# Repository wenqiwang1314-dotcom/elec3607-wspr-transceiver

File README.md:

# ELEC3607 Assignment 1: WSPR Transceiver 任务设计

版本依据：Assignment 1 - WSPR Transceiver Version 0.4, 15 Apr 2026  
工程目录：`pcb_2026`  
原始 KiCad 工程：`bbb.kicad_pro`, `bbb.kicad_sch`, `bbb.kicad_pcb`  
最终提交：单个 `.zip`，包含 KiCad schematic、PCB design files、IEEE conference format 报告。

## 1. 项目目标

本项目在实验课 WSPR-SDR 接收机基础上完成两个修改：

1. Part A：用 Si5351 剩余的 `CLK2` 输出实现 WSPR 发射软件，并通过硬连线 RF loopback 让已有接收机或教师 decoder board 解码。
2. Part B：从现有 PCB 出发，重新设计成收发一体 transceiver PCB。发射机输出需达到 `0.1 W into 50 ohms`，收发共用接收机 bandpass filter，收发切换由 GPIO 控制，新增器件来自 Element14 Australia。

评分重点不是解释旧 WSPR-SDR，而是清楚说明新增发射功能、RF loopback、功率放大、收发切换和 PCB 修改如何工作。

## 2. 本地 Resources 使用清单

| 资料 | 用途 |
|---|---|
| `Resources/wspr_coding_process.pdf` | Part A WSPR message 编码、symbol 生成、tone mapping 的主要依据。 |
| `Resources/Si5351-B.pdf` | Si5351 `CLK2` 输出频率、驱动强度、寄存器/I2C 控制和硬件限制。 |
| `Resources/QS11-2010-Taylor.pdf` | WSPR 协议背景、4-FSK、tone spacing、解码约束和报告引用。 |
| `Resources/Tayloe_mixer_x3a.pdf` | 原接收机 quadrature sampling/Tayloe mixer 信号路径说明。 |
| `Resources/A Comparison of Affordable, Self-Assembled Software-Defined Radio Receivers Using Quadrature Sampling Down-Conversion.pdf` | 报告风格和 SDR 接收架构描述参考。 |
| `Resources/ABCs of Probes 60W-6053-15.pdf` | 示波器探头、RF/低电平测量误差说明。 |
| `Resources/emc_and_signal_integrity_ce_magazine_march-april_1999.pdf` | PCB layout、RF grounding、return path 和串扰风险说明。 |
| `Resources/website.txt` | WSPR/SDR 相关网页入口。 |

## 3. 团队分工建议

| 角色 | 主要负责 | 输出物 |
|---|---|---|
| Software lead | `wspr_transmit` C 程序、WSPR 编码、Si5351 `CLK2` 控制、CLI 参数验证 | C 源码、运行说明、软件测试记录 |
| Hardware modification lead | Part A 现有 PCB 飞线/RF loopback/衰减网络/照片/测量 | 修改原理图、PCB 照片、测试数据 |
| RF/PCB lead | Part B PA、T/R switch、共享 BPF、KiCad schematic/PCB layout | 更新后的 `.kicad_sch`, `.kicad_pcb`, BOM |
| Report/integration lead | IEEE 报告、图表、参考文献、提交 zip 检查 | 4 页以内 PDF 报告、最终 zip |

每个人都需要能在 oral discussion 中解释自己部分之外的完整信号路径。

## 4. Part A 任务：WSPR 发射与 RF Loopback

### A1. 明确 WSPR 发射需求

- 输入格式：`./wspr_transmit CALLSIGN LOCATOR POWER`
- 示例：`./wspr_transmit VK2AAX QF56 3`
- CLI 参数检查：
  - callsign：合法 WSPR callsign 格式，报告中说明支持范围。
  - locator：4 字符 Maidenhead grid，例如 `QF56`。
  - power：WSPR dBm power code，示例 `3` 代表作业要求输入格式，实际含义需在报告中解释。
- 输出信号：
  - WSPR uses 4-FSK.
  - 每个 symbol 选择 4 个 tone 之一。
  - tone spacing 约 `1.4648 Hz`。
  - 一帧 WSPR 标准消息共 `162` symbols，持续约 `110.6 s`。
- 软件必须使用 Si5351 `CLK2` 产生 RF tone，不使用空中发射。

完成标准：

- 程序能接受示例命令并生成确定的 WSPR symbol/tone 序列。
- 参数错误时给出 usage。
- 报告中给出 symbol generation 流程图或伪代码。

### A2. 编写 `wspr_transmit` C 程序

建议文件：

- `software/wspr_transmit.c`
- `software/wspr_encode.c`
- `software/wspr_encode.h`
- `software/si5351_control.c`
- `software/si5351_control.h`
- `software/Makefile`

软件模块任务：

1. `main()` 解析 `CALLSIGN LOCATOR POWER`。
2. WSPR message packing：将 callsign、locator、power 打包成 WSPR message bits。
3. FEC/interleaving/sync：按 `Resources/wspr_coding_process.pdf` 生成 162 个 symbols。
4. Tone scheduler：将 symbol 映射到 `f0 + symbol * 1.4648 Hz`。
5. Si5351 driver：通过 I2C 更新 `CLK2` 输出频率。
6. Timing：每个 symbol 周期约 `110.592 / 162 = 0.6827 s`，尽量减少切换抖动。
7. Logging：启动时打印 callsign、locator、power、base frequency、frame start time。

建议测试：

- Unit test：固定输入 `VK2AAX QF56 3` 时 symbol 序列可重复。
- Dry run：不控制 Si5351，只打印 tone frequency 和 symbol index。
- Hardware run：连接示波器/频率计确认 `CLK2` 有 4 个细小频偏。

完成标准：

- `make` 后生成 `wspr_transmit`。
- `./wspr_transmit VK2AAX QF56 3` 能运行完整帧。
- 报告附核心 C 代码片段，不必粘贴全部文件。

### A3. 音频 loopback 小步验证

用途：在 RF loopback 之前先验证编码和解码链路。

任务：

- 生成等效 audio baseband 4-FSK tone 序列。
- 将 audio 输出接入现有接收/解码链路。
- 用实验室 receiver/decoder 确认 callsign、locator、power 可解出。

完成标准：

- 记录一次成功 decode 的截图或串口/终端输出。
- 在报告中说明 audio loopback 只是中间验证，不是最终 RF 方案。

### A4. RF loopback 硬件修改

目标：将 Si5351 `CLK2` RF 输出硬连线接回 receiver RF input，不经过天线空中传播。

建议电路：

```text
Si5351 CLK2
    |
    |-- DC blocking capacitor
    |
  resistive attenuator / level-setting network
    |
    |-- optional test point
    |
receiver RF input before existing bandpass/mixer chain
```

关键设计点：

- 不应直接把过大的 `CLK2` 方波灌入 receiver input。
- 通过电容隔直和电阻衰减控制接收机输入电平。
- 尽量保持短接线、公共地可靠、避免 RF pickup。
- 报告需要包含：
  - 修改电路图。
  - 修改后 PCB 照片。
  - 衰减网络计算。
  - 实测 `CLK2` 输出幅度、receiver input 幅度、decode 结果。

完成标准：

- 教师 decoder board 或本组 WSPR receiver 能从 RF loopback 解码。
- 测量记录包含仪器型号/探头设置/测量点。

### A5. Part A 测量清单

| 测量项 | 测量点 | 期望记录 |
|---|---|---|
| `CLK2` RF 输出 | Si5351 `CLK2` 或飞线起点 | 频率、幅度、波形 |
| 衰减后 RF | receiver input | 幅度，确认不会过载 |
| Tone spacing | `CLK2` 或 receiver output | 约 `1.4648 Hz` 间隔，或解释仪器分辨率限制 |
| Decode 结果 | WSPR receiver/decoder | callsign、locator、power、SNR/time offset/frequency offset |
| 电源电流 | 板级输入 | RX/TX 状态对比 |

## 5. Part B 任务：Transceiver PCB 设计

### B1. 建立 KiCad 修改分支

任务：

- 复制原始工程，避免破坏 baseline。
- 建议新文件命名：
  - `wspr_transceiver.kicad_pro`
  - `wspr_transceiver.kicad_sch`
  - `wspr_transceiver.kicad_pcb`
- 保持 PCB 外形尺寸与原始 `bbb.kicad_pcb` 一致。
- 保留原接收机必要链路，只修改收发相关电路。

完成标准：

- KiCad ERC/DRC 主要错误已处理或在报告中解释。
- 原始板框尺寸未改变。

### B2. Part B RF 信号路径定义

建议完整信号路径：

```text
TX mode:
Si5351 CLK2
 -> output shaping / attenuator
 -> driver / PA
 -> low-pass or harmonic filtering if required
 -> GPIO-controlled T/R switch
 -> shared bandpass filter
 -> 50 ohm RF output / loopback/test connector

RX mode:
50 ohm RF input
 -> GPIO-controlled T/R switch
 -> shared bandpass filter
 -> existing receiver mixer / audio chain
```

报告必须说明：

- GPIO 为 RX 时，PA 输出不能反灌 receiver。
- GPIO 为 TX 时，receiver input 被隔离或保护。
- Bandpass filter 被 TX 和 RX 共用，符合题目要求。
- 50 ohm 系统如何匹配。

### B3. 0.1 W into 50 ohms 设计计算

设计目标：

- 输出功率：`Pout = 0.1 W = 20 dBm`
- 负载：`R = 50 ohms`
- 正弦波等效：
  - `Vrms = sqrt(P * R) = sqrt(0.1 * 50) = 2.236 V`
  - `Vpk = 3.162 V`
  - `Vpp = 6.324 V`
  - `Irms = Vrms / R = 44.7 mA`

任务：

- 选择 PA 架构：小信号 driver + RF transistor/MOSFET，或可买到的 RF gain block/PA 器件。
- 计算所需 gain：由 Si5351 `CLK2` 可用输出电平推算到 `20 dBm`。
- 设计输出匹配网络和 bias。
- 检查功耗和热耗散。
- 检查 harmonic suppression，必要时加入 LPF 或利用共享 BPF 后的选择性。

完成标准：

- 报告给出 PA 电路图、关键元件值、偏置点、预期 gain、预期输出功率。
- BOM 中新增器件来自 Element14 Australia，并记录订购编号、封装、库存检查日期。

### B4. GPIO 控制收发切换

可选方案：

1. RF switch IC：GPIO 直接/经电平转换控制，优点是隔离度和插损明确。
2. 二极管/模拟开关方案：成本低，但需要认真计算 RF 隔离、插损和偏置。
3. 小继电器：隔离好，但体积、电流、切换速度和 PCB 尺寸可能不利。

任务：

- 确定 GPIO 电压标准和可用 pin。
- 设计默认安全状态：上电默认 RX 或 TX disabled。
- 增加 PA enable，避免 RX 时 PA 自激或泄漏。
- 在原理图中清楚标注 `TX_EN` 或 `TR_CTRL`。

完成标准：

- 原理图中可从 GPIO 追踪到 RF switch/PA enable。
- 报告给出 TX/RX 两种状态的开关真值表。

示例真值表：

| GPIO `TR_CTRL` | 模式 | PA | RF path |
|---|---|---|---|
| `0` | RX | Off | RF input -> BPF -> receiver |
| `1` | TX | On | PA -> BPF -> RF output |

### B5. PCB layout 修改任务

任务：

- 保持原 PCB 大小和安装孔。
- PA 到 RF connector 的路径短、宽度接近 50 ohm 微带线要求。
- PA 输出和 receiver input 保持物理隔离。
- RF switch 靠近 BPF 或 RF connector，减少 stub。
- PA 电源就近放置 decoupling capacitors。
- 高电流/高频回流路径下方保持连续地。
- 增加测试点：
  - `TP_CLK2`
  - `TP_PA_IN`
  - `TP_PA_OUT`
  - `TP_TR_CTRL`
  - `TP_RX_IN`

完成标准：

- KiCad DRC 通过，或每个剩余 issue 都有理由。
- 关键 RF 网络可在 PCB 上清楚追踪。
- 生成 Gerber/Drill/BOM/position files 供提交或制造参考。

### B6. Element14 器件选择任务

需要记录每个新增器件：

- Manufacturer part number
- Element14 order code
- Package/footprint
- Datasheet URL
- 关键参数：频率范围、gain、P1dB/output power、supply voltage、insertion loss/isolation/current rating
- 查询日期

候选类别：

- RF amplifier / transistor / MOSFET
- RF switch 或 PIN diode
- Matching inductors/capacitors
- Attenuator resistors
- RF connector / test point
- Power decoupling capacitors

注意：库存和价格会变化，最终报告中要写明查询日期。

## 6. 报告结构建议（IEEE Conference Format，最多 4 页）

建议页数分配：

| 部分 | 建议长度 | 内容 |
|---|---:|---|
| Title/Abstract | 0.25 页 | 一句话说明实现了 RF loopback transmitter 和 transceiver PCB redesign。 |
| I. Introduction | 0.25 页 | 项目目标、频段、WSPR-SDR 到 transceiver 的变化。 |
| II. Part A Transmitter Implementation | 1.25 页 | WSPR 编码、`CLK2` 发射、CLI、RF loopback、衰减计算、软件/硬件框图。 |
| III. Part A Measurements | 0.5 页 | 波形、频率、电平、decode 结果、照片。 |
| IV. Part B Transceiver Hardware | 1.25 页 | PA、0.1 W 计算、T/R switch、共享 BPF、GPIO 真值表、完整信号路径。 |
| V. PCB Layout and Expected Performance | 0.5 页 | PCB 截图、RF layout 决策、预期功率/隔离/风险。 |
| References | 0.25 页 | WSPR、Si5351、器件 datasheet、Resources 中论文。 |

报告中必须放在正文的证据：

- Part A 修改电路图。
- Part A 修改后 PCB 照片。
- `wspr_transmit` 核心 C 代码。
- Part A 测量数据和 decode 结果。
- Part B 完整 schematic。
- Part B PA 和 50 ohm 功率计算。
- Part B PCB layout 截图。
- 新增器件 BOM。

## 7. 最终提交检查表

- [ ] `wspr_transmit` C 源码和 Makefile 已包含在 zip 中。
- [ ] `./wspr_transmit VK2AAX QF56 3` 已测试。
- [ ] RF loopback 修改电路图已画出。
- [ ] 修改后 PCB 照片已放入报告。
- [ ] 至少一次 WSPR decode 成功结果已记录。
- [ ] Part B KiCad schematic 已更新。
- [ ] Part B PCB layout 已更新且板框尺寸不变。
- [ ] PA 设计目标达到 `0.1 W into 50 ohms`，计算写入报告。
- [ ] T/R switch 由 GPIO 控制，真值表写入报告。
- [ ] 新增器件均来自 Element14 Australia，BOM 包含 order code。
- [ ] ERC/DRC 已运行，剩余问题已解释。
- [ ] IEEE conference format 报告不超过 4 页。
- [ ] zip 中包含 report PDF、KiCad files、source code、必要图片/测量数据。

## 8. 风险与应对

| 风险 | 影响 | 应对 |
|---|---|---|
| WSPR 编码实现错误 | decoder 无法解码 | 先做 dry-run 和 audio loopback，再做 RF loopback。 |
| Si5351 频率更新时间抖动 | tone 不稳定，SNR 下降 | 预先计算 tone frequencies，symbol 边界只做必要 I2C 更新。 |
| RF loopback 电平过高 | receiver overload 或损坏 | 加电容隔直和可计算衰减网络，先从大衰减开始测试。 |
| PA harmonic 太高 | 输出不干净，decoder 测试失败 | 使用共享 BPF，必要时在 PA 后加 LPF。 |
| T/R switch 隔离不足 | TX 泄漏进 RX 或 RX 灵敏度下降 | 选择隔离度足够的 RF switch，layout 缩短 stub。 |
| PCB 尺寸限制 | 新增 PA/switch 放不下 | 优先使用小封装器件，并移除不必要测试结构。 |
| Element14 缺货 | BOM 不可采购 | 尽早锁定 2 个可替代器件并记录查询日期。 |

## 9. 建议时间线

| 时间 | 软件 | 硬件/PCB | 报告 |
|---|---|---|---|
| Day 1 | 完成 WSPR 编码资料阅读和代码框架 | 找到 `CLK2`、receiver input、可用 GPIO | 建立报告模板 |
| Day 2 | 完成 symbol 生成和 dry-run | 设计 Part A 衰减/loopback 电路 | 画 Part A 框图 |
| Day 3 | 接入 Si5351 `CLK2` 控制 | 焊接 Part A 修改并拍照 | 写 Part A 方法 |
| Day 4 | audio/RF loopback debug | 完成 Part B PA 和 T/R switch 原理图 | 加入测量表 |
| Day 5 | 整理代码和运行说明 | 完成 PCB layout 和 ERC/DRC | 写 Part B 设计 |
| Day 6 | 最终复测 | 生成 Gerber/BOM/截图 | 压缩到 4 页并交叉检查 |

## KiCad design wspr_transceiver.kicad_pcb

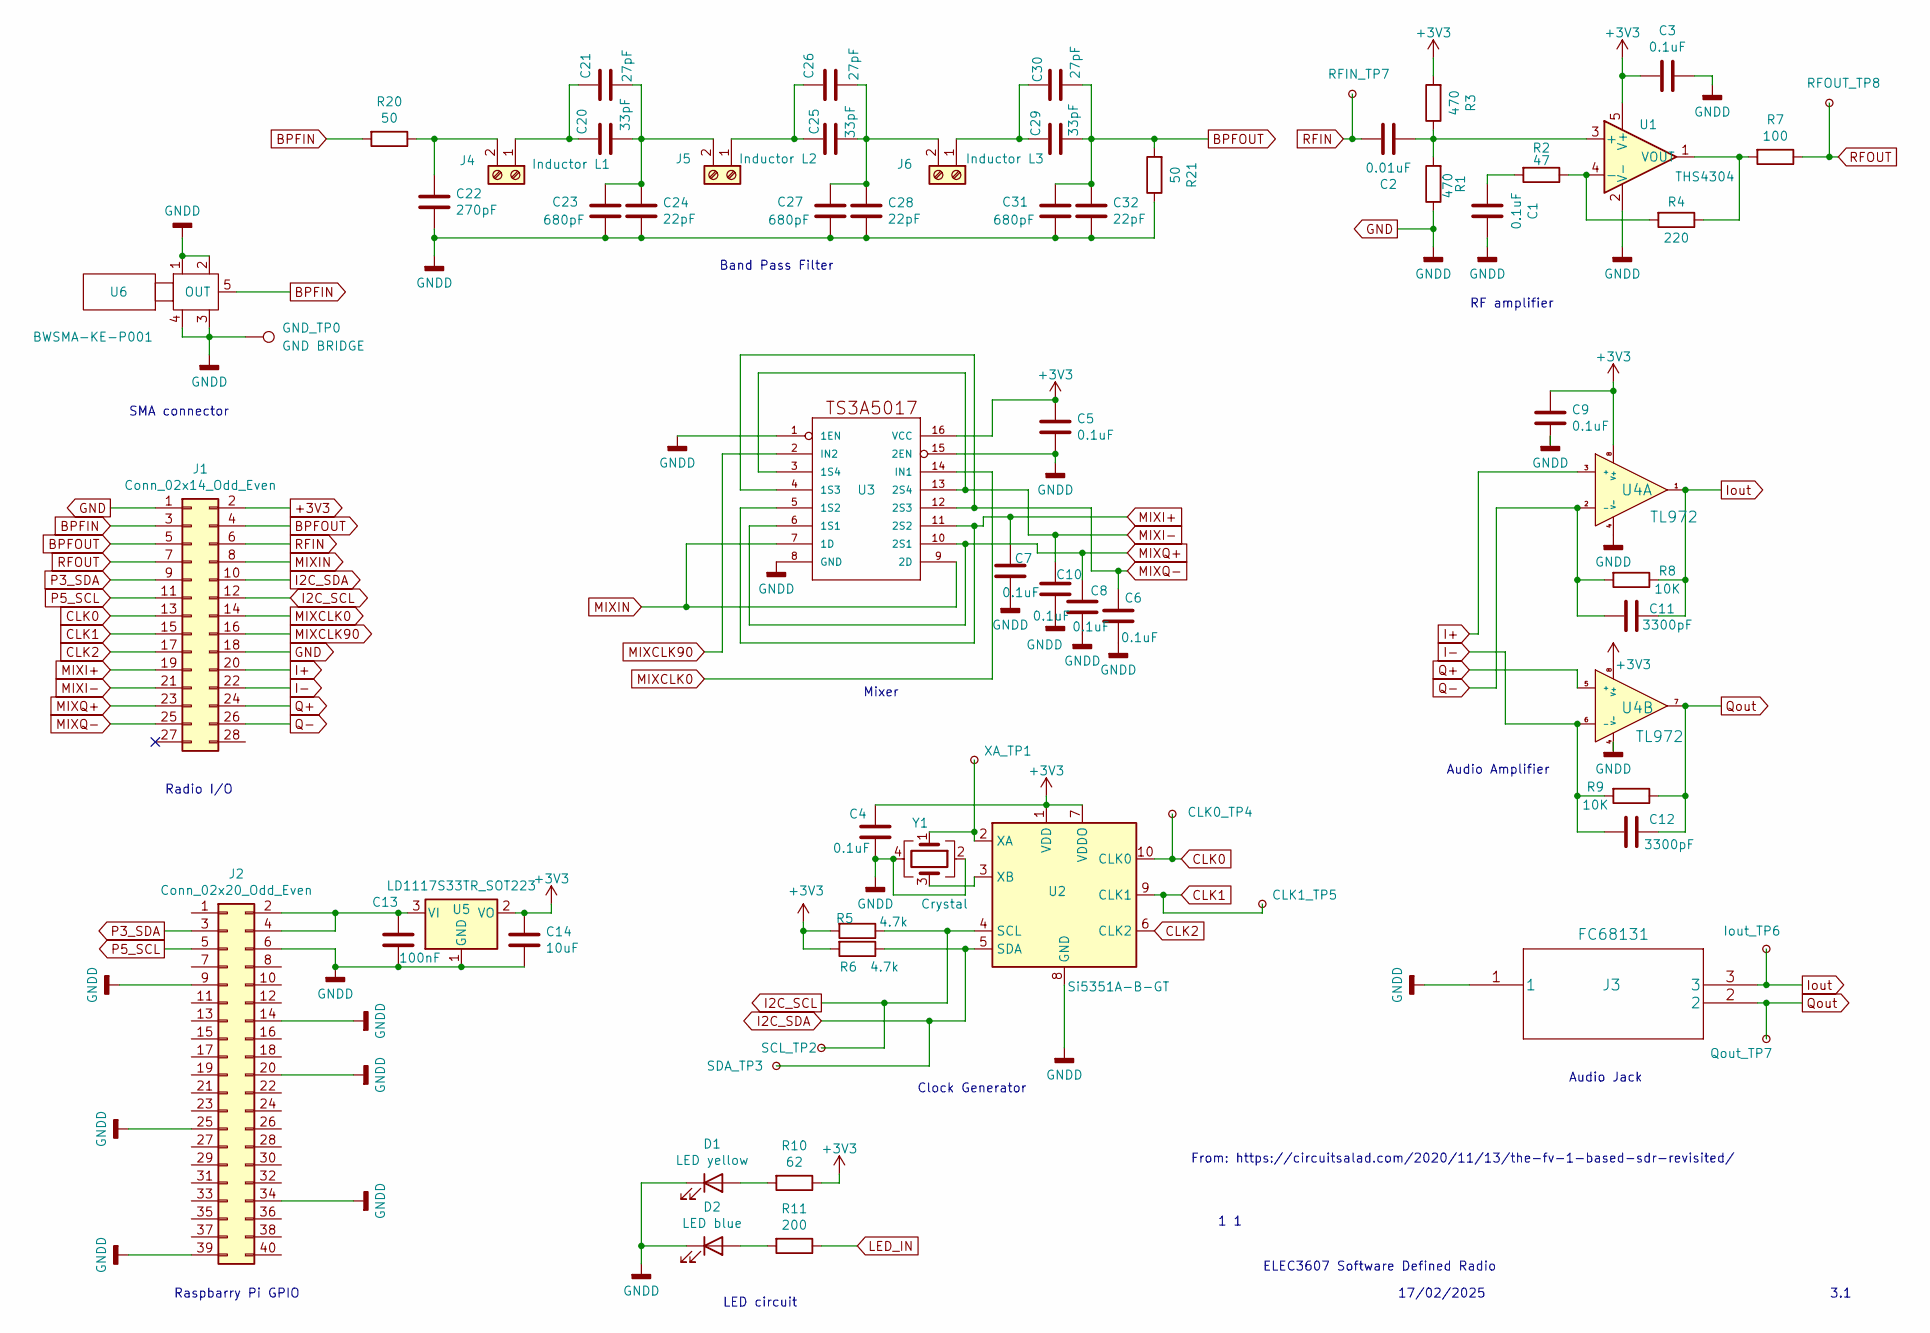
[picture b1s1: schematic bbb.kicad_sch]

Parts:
C1, C3, C4, C5, C6, C7, C8, C9, C10: 0.1uF; C_0805_2012Metric
C2: 0.01uF; C_0805_2012Metric
C11, C12: 3300pF; C_0805_2012Metric
C13: 100nF; C_0805_2012Metric
C14: 10uF; C_0805_2012Metric
C20, C25, C29: 33pF; C_0805_2012Metric
C21, C26, C30: 27pF; C_0805_2012Metric
C22: 270pF; C_0805_2012Metric
C23, C27, C31: 680pF; C_0805_2012Metric
C24, C28, C32: 22pF; C_0805_2012Metric
CLK0_TP4, CLK1_TP5: TestPoint_Small; TestPoint_Keystone_5000-5004_Miniature
D1: LED yellow; D_0603_1608Metric
D2: LED blue; D_0603_1608Metric
GND_TP0: GND BRIDGE; TestPoint_Bridge_Pitch7.62mm_Drill1.3mm
Iout_TP6: TestPoint_Small; TestPoint_Keystone_5000-5004_Miniature
J1: Conn_02x14_Odd_Even; PinHeader_2x14_P2.54mm_Vertical
J2: Conn_02x20_Odd_Even; PinHeader_2x20_P2.54mm_Vertical
J3: FC68131
J4: Inductor L1; TerminalBlock_Phoenix_MPT-0,5-2-2.54_1x02_P2.54mm_Horizontal
J5: Inductor L2; TerminalBlock_Phoenix_MPT-0,5-2-2.54_1x02_P2.54mm_Horizontal
J6: Inductor L3; TerminalBlock_Phoenix_MPT-0,5-2-2.54_1x02_P2.54mm_Horizontal
Qout_TP7: TestPoint_Small; TestPoint_Keystone_5000-5004_Miniature
R1, R3: 470; R_0805_2012Metric
R2: 47; R_0805_2012Metric
R4: 220; R_0805_2012Metric
R5, R6: 4.7k; R_0805_2012Metric
R7: 100; R_0805_2012Metric
R8, R9: 10K; R_0805_2012Metric
R10: 62; R_0805_2012Metric
R11: 200; R_0805_2012Metric
R20, R21: 50; R_0805_2012Metric
RFIN_TP7: TestPoint_Small; TestPoint_Keystone_5000-5004_Miniature
RFOUT_TP8: TestPoint_Small; TestPoint_Keystone_5000-5004_Miniature
SCL_TP2: TestPoint_Small; TestPoint_Keystone_5000-5004_Miniature
SDA_TP3: TestPoint_Small; TestPoint_Keystone_5000-5004_Miniature
U1: THS4304; SOT-23-5
U2: Si5351A-B-GT; MSOP-10_3x3mm_P0.5mm
U3: TS3A5017; SOIC-16_3.9x9.9mm_P1.27mm
U4: TL972; SOIC-8-1EP_3.9x4.9mm_P1.27mm_EP2.29x3mm
U5: LD1117S33TR_SOT223; SOT-223-3_TabPin2
U6: BWSMA-KE-P001
XA_TP1: TestPoint_Small; TestPoint_Keystone_5000-5004_Miniature
Y1: Crystal; Crystal_SMD_TXC_7M-4Pin_3.2x2.5mm

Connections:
+3V3: C3.2, C4.1, C5.1, C9.1, C14.1, J1.2, R3.2, R5.2, R6.2, R10.1, U1.5 (V+), U2.1 (VDD), U2.7 (VDDO), U3.16 (VCC), U4.8 (V+), U5.2 (VO)
BPFIN: J1.3, R20.2, U6.5 (OUT)
BPFOUT: C29.2, C30.2, C31.1, C32.1, J1.4, J1.5, R21.2
CLK0: CLK0_TP4.1, J1.13, U2.10 (CLK0)
CLK1: CLK1_TP5.1, J1.15, U2.9 (CLK1)
CLK2: J1.17, U2.6 (CLK2)
GND: C1.1, C3.1, C4.2, C5.2, C6.2, C7.2, C8.2, C9.2, C10.2, C13.2, C14.2, C22.2, C23.2, C24.2, C27.2, C28.2, C31.2, C32.2, D1.1 (K), D2.1 (K), GND_TP0.1, J1.1, J1.18, J2.6, J2.9, J2.14, J2.20, J2.25, J2.34, J2.39, J3.1, R1.1, R21.1, U1.2 (V-), U2.8 (GND), U3.1 (1EN), U3.8 (GND), U3.15 (2EN), U4.4 (V-), U5.1 (GND), U6.1, U6.2, U6.3, U6.4, Y1.2, Y1.4
I2C_SCL: J1.12, R5.1, SCL_TP2.1, U2.4 (SCL)
I2C_SDA: J1.10, R6.1, SDA_TP3.1, U2.5 (SDA)
I+: J1.20, U4.3 (+)
I-: C12.2, J1.22, R9.2, U4.6 (-)
Iout: C11.1, Iout_TP6.1, J3.3, R8.1, U4.1
LED_IN: R11.1
MIXCLK0: J1.14, U3.14 (IN1)
MIXCLK90: J1.16, U3.2 (IN2)
MIXI+: C7.1, J1.19, U3.5 (1S2), U3.11 (2S2)
MIXI-: C10.1, J1.21, U3.3 (1S4), U3.13 (2S4)
MIXIN: J1.8, U3.7 (1D), U3.9 (2D)
MIXQ+: C8.1, J1.23, U3.6 (1S1), U3.10 (2S1)
MIXQ-: C6.1, J1.25, U3.4 (1S3), U3.12 (2S3)
unnamed: C1.2, R2.2
unnamed: D1.2 (A), R10.2
unnamed: D2.2 (A), R11.2
unnamed: C13.1, J2.2, J2.4, U5.3 (VI)
unnamed: C20.1, C21.1, J4.1
unnamed: C22.1, J4.2, R20.1
unnamed: C25.1, C26.1, J5.1
unnamed: C20.2, C21.2, C23.1, C24.1, J5.2
unnamed: C29.1, C30.1, J6.1
unnamed: C25.2, C26.2, C27.1, C28.1, J6.2
unnamed: C2.2, R1.2, R3.1, U1.3 (+)
unnamed: R2.1, R4.2, U1.4 (-)
unnamed: R4.1, R7.2, U1.1 (VOUT)
unnamed: U2.2 (XA), XA_TP1.1, Y1.1
unnamed: U2.3 (XB), Y1.3
P3_SDA: J1.9, J2.3
P5_SCL: J1.11, J2.5
Q+: J1.24, U4.5 (+)
Q-: C11.2, J1.26, R8.2, U4.2 (-)
Qout: C12.1, J3.2, Qout_TP7.1, R9.1, U4.7
RFIN: C2.1, J1.6, RFIN_TP7.1
RFOUT: J1.7, R7.1, RFOUT_TP8.1

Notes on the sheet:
Audio Amplifier
LED circuit
SMA connector
Raspbarry Pi GPIO
Audio Jack
17/02/2025
Radio I/O
Clock Generator
ELEC3607 Software Defined Radio
3.1
From: https://circuitsalad.com/2020/11/13/the-fv-1-based-sdr-revisited/
Band Pass Filter
Mixer
1 1
RF amplifier

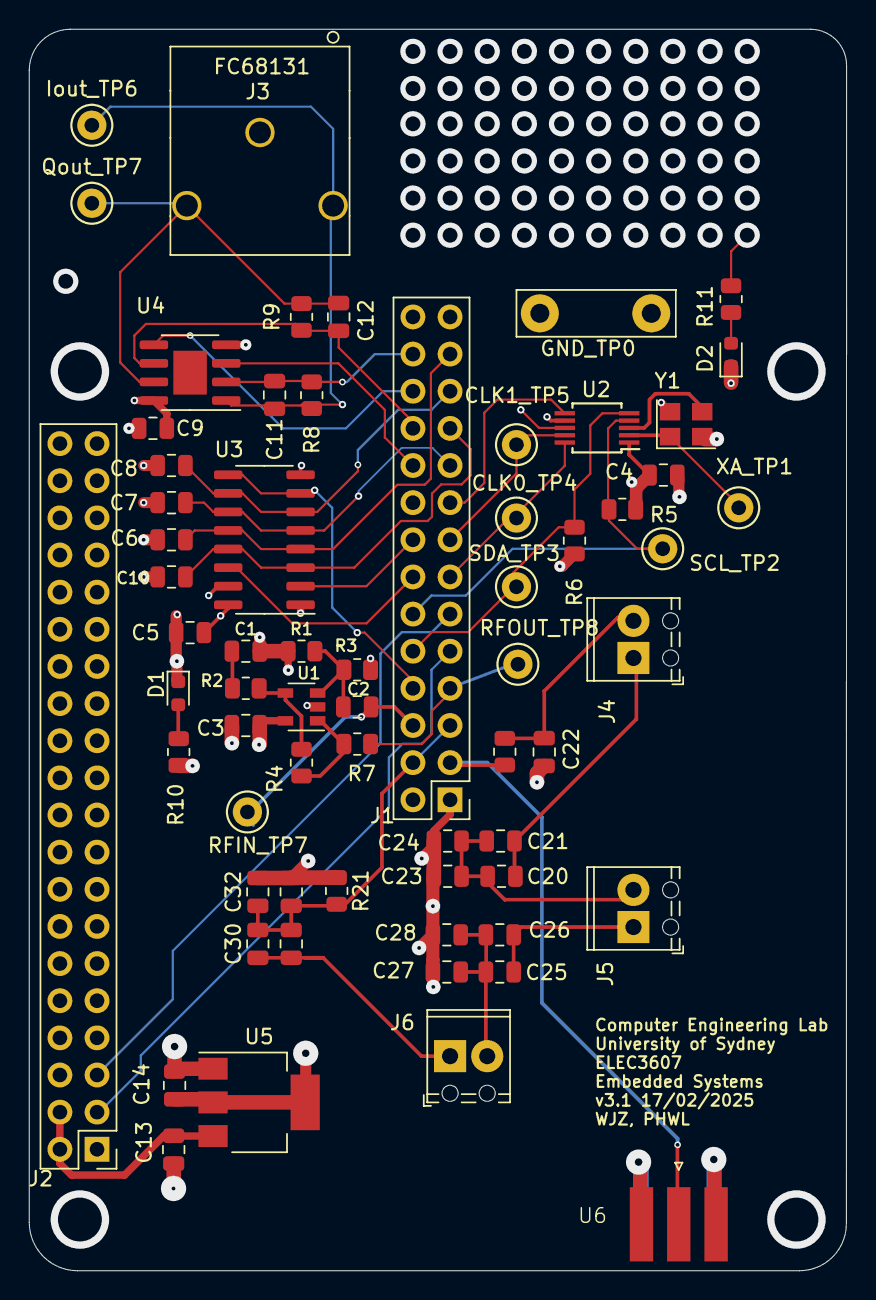
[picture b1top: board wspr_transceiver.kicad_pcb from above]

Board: 4 copper layers, 55.9 x 84.9 mm, 65 parts (0 on the bottom side), 41 nets.

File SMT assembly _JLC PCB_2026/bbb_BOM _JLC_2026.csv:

Comment,Designator,Footprint
0.1uF,"C1,C3,C4,C5,C6,C7,C8,C9,C10",Capacitor_SMD:C_0805_2012Metric
0.01uF,C2,Capacitor_SMD:C_0805_2012Metric
3300pF,"C11,C12",Capacitor_SMD:C_0805_2012Metric
100nF,C13,Capacitor_SMD:C_0805_2012Metric
10uF,C14,Capacitor_SMD:C_0805_2012Metric
33pF,"C20,C25,C29",Capacitor_SMD:C_0805_2012Metric
27pF,"C21,C26,C30",Capacitor_SMD:C_0805_2012Metric
270pF,C22,Capacitor_SMD:C_0805_2012Metric
680pF,"C23,C27,C31",Capacitor_SMD:C_0805_2012Metric
22pF,"C24,C28,C32",Capacitor_SMD:C_0805_2012Metric
TestPoint_Small,"CLK0_TP4,CLK1_TP5,Iout_TP6,Qout_TP7,RFIN_TP7,RFOUT_TP8,SCL_TP2,SDA_TP3,XA_TP1",TestPoint:TestPoint_Keystone_5000-5004_Miniature
LED yellow,D1,Diode_SMD:D_0603_1608Metric
LED blue,D2,Diode_SMD:D_0603_1608Metric
GND BRIDGE,GND_TP0,TestPoint:TestPoint_Bridge_Pitch7.62mm_Drill1.3mm
Conn_02x14_Odd_Even,J1,Connector_PinHeader_2.54mm:PinHeader_2x14_P2.54mm_Vertical
Conn_02x20_Odd_Even,J2,Connector_PinHeader_2.54mm:PinHeader_2x20_P2.54mm_Vertical
FC68131,J3,AudioJack:FC68131
Inductor L1,J4,"TerminalBlock_Phoenix:TerminalBlock_Phoenix_MPT-0,5-2-2.54_1x02_P2.54mm_Horizontal"
Inductor L2,J5,"TerminalBlock_Phoenix:TerminalBlock_Phoenix_MPT-0,5-2-2.54_1x02_P2.54mm_Horizontal"
Inductor L3,J6,"TerminalBlock_Phoenix:TerminalBlock_Phoenix_MPT-0,5-2-2.54_1x02_P2.54mm_Horizontal"
470,"R1,R3",Resistor_SMD:R_0805_2012Metric
47,R2,Resistor_SMD:R_0805_2012Metric
220,R4,Resistor_SMD:R_0805_2012Metric
4.7k,"R5,R6",Resistor_SMD:R_0805_2012Metric
100,R7,Resistor_SMD:R_0805_2012Metric
10K,"R8,R9",Resistor_SMD:R_0805_2012Metric
62,R10,Resistor_SMD:R_0805_2012Metric
200,R11,Resistor_SMD:R_0805_2012Metric
50,"R20,R21",Resistor_SMD:R_0805_2012Metric
THS4304,U1,Package_TO_SOT_SMD:SOT-23-5
Si5351A-B-GT,U2,Package_SO:MSOP-10_3x3mm_P0.5mm
TS3A5017,U3,Package_SO:SOIC-16_3.9x9.9mm_P1.27mm
TL972,U4,Package_SO:SOIC-8-1EP_3.9x4.9mm_P1.27mm_EP2.29x3mm
LD1117S33TR_SOT223,U5,Package_TO_SOT_SMD:SOT-223-3_TabPin2
BWSMA-KE-P001,U6,BWSMA-KE-P001:BWSMA-KE-P001
Crystal,Y1,Crystal:Crystal_SMD_TXC_7M-4Pin_3.2x2.5mm

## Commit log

2026-05-03 Initial WSPR transceiver project files
2026-05-03 Initialize README for WSPR Transceiver project
    Add detailed project description and task breakdown for ELEC3607 Assignment 1 involving WSPR Transceiver design.
2026-05-03 Add hardware execution steps
2026-05-03 Create transceiver KiCad project copy
2026-05-03 Document hardware architecture from schematic image
2026-05-06 Document Part A receiver overload attenuation
2026-05-06 Add Part A 30mVpp input reference calculation
2026-05-06 Correct Part A receiver reference frequency

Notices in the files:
parts and their libraries:
Copyright 2021 Accelerated Designs. All rights reserved.
